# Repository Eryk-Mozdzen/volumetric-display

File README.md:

# Volumetric Display
Design inspired from [mitxela](https://www.youtube.com/watch?v=HKpBhE7QVAI).

### Specs
- STM32F030 microcontroller
- 8x8 led matrix
- CNY70 IR sensor
- 2x CR3032 power source

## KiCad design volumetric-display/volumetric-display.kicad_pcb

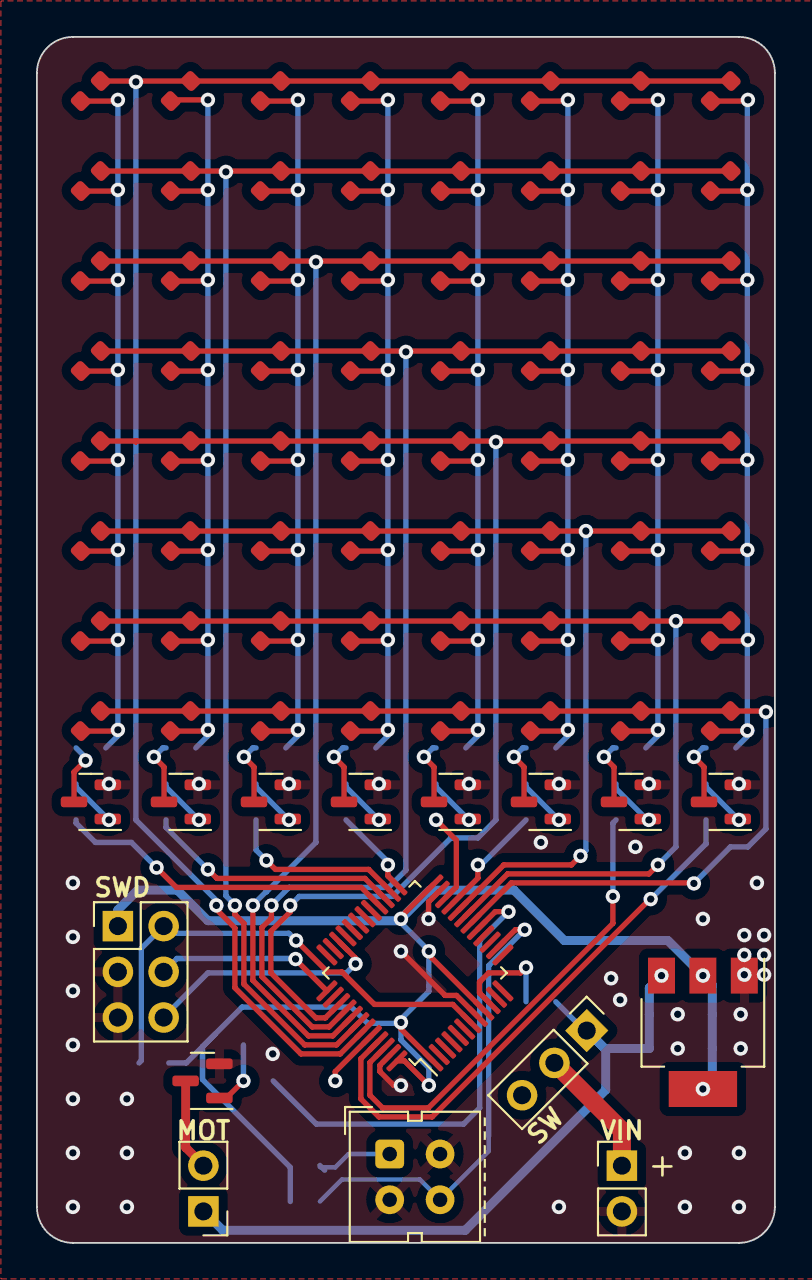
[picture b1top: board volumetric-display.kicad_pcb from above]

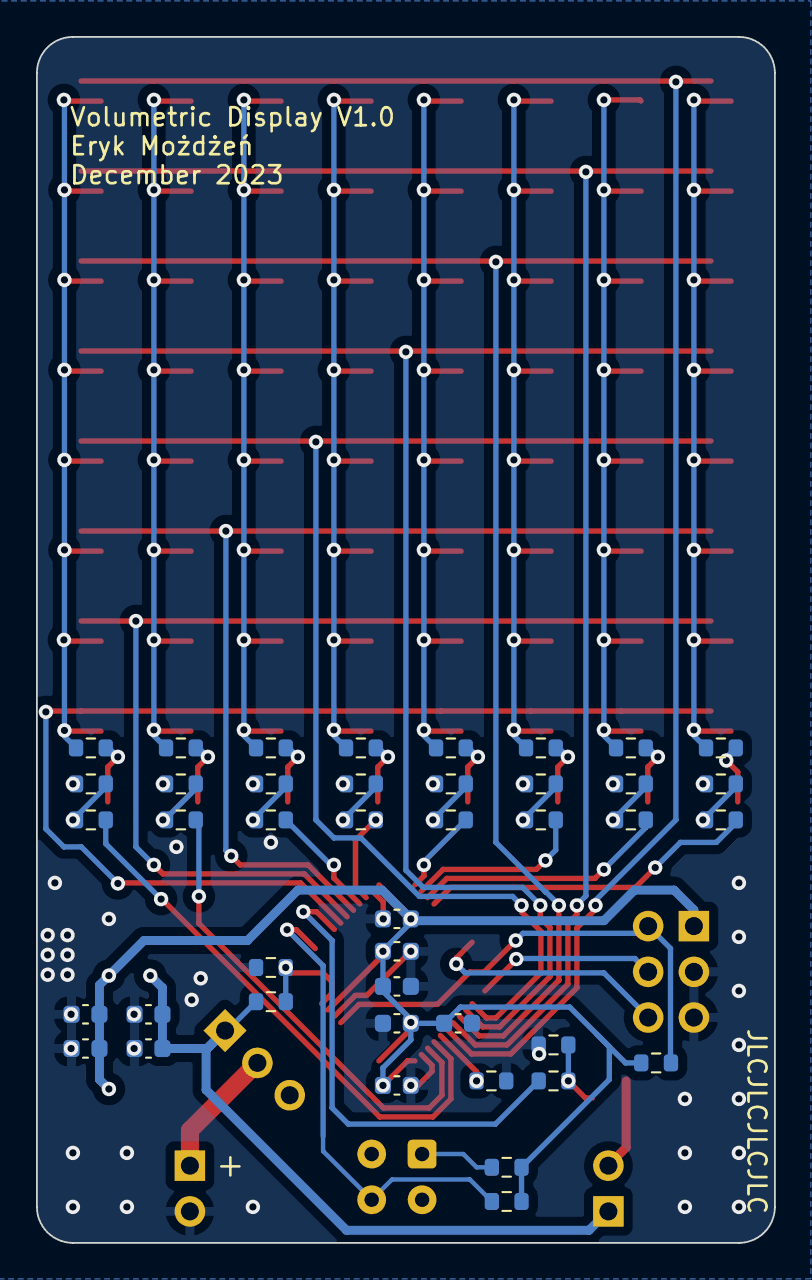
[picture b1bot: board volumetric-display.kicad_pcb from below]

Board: 2 copper layers, 41.0 x 67.0 mm, 122 parts (42 on the bottom side), 54 nets.

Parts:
C1, C7, C10: 4u7; C_0603_1608Metric
C2, C3, C4, C8, C9: 100n; C_0603_1608Metric
C5: 10n; C_0603_1608Metric
C6: 1u; C_0603_1608Metric
D1, D2, D3, D4, D5, D6, D7, D8, D9, D10, D11, D12, D13, D14, D15, D16, D17, D18, D19, D20, D21, D22, D23, D24, D25, D26, D27, D28, D29, D30, D31, D32, D33, D34, D35, D36, D37, D38, D39, D40, D41, D42, D43, D44, D45, D46, D47, D48, D49, D50, D51, D52, D53, D54, D55, D56, D57, D58, D59, D60, D61, D62, D63, D64: LED; led_0603
J1: Conn_02x03_Odd_Even; PinHeader_2x03_P2.54mm_Vertical
J2, J3: Conn_01x02; PinHeader_1x02_P2.54mm_Vertical
Q1, Q2, Q3, Q4, Q5, Q6, Q7, Q8, Q9: BSS138; SOT-23
R1, R7, R9, R10, R11, R12, R13, R14, R15, R16, R17, R18, R19, R20, R25, R26, R27, R28: 500; R_0603_1608Metric
R2, R3, R4, R8, R21, R22, R23, R24, R29, R30, R31, R32: 10k; R_0603_1608Metric
R5, R6: 100k; R_0603_1608Metric
SW1: SW_Push_SPDT; PinHeader_1x03_P2.54mm_Vertical
U1: CNY70; Vishay_CNY70
U2: STM32F030C8Tx; LQFP-48_7x7mm_P0.5mm
U3: LM1117MP-3.3; SOT-223-3_TabPin2

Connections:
+3.3V: C1.1, C2.1, C3.1, C4.1, C5.1, C6.1, C9.1, C10.1, J1.1, R1.1, R2.1, R3.2, U2.1 (VDD), U2.9 (VDDA), U2.24 (VDD), U2.48 (VDD), U3.2 (VO)
+BATT: C7.1, C8.1, J2.1, R5.1, SW1.1 (A), U3.3 (VI)
/BATT_SENSE: R5.2, R6.1, U2.10 (PA0)
/MATRIX_COL0: R17.1, U2.28 (PB15)
/MATRIX_COL1: R18.1, U2.27 (PB14)
/MATRIX_COL2: R19.1, U2.26 (PB13)
/MATRIX_COL3: R20.1, U2.25 (PB12)
/MATRIX_COL4: R25.1, U2.22 (PB11)
/MATRIX_COL5: R26.1, U2.21 (PB10)
/MATRIX_COL6: R27.1, U2.46 (PB9)
/MATRIX_COL7: R28.1, U2.45 (PB8)
/MATRIX_ROW0: D1.2 (A), D2.2 (A), D3.2 (A), D4.2 (A), D5.2 (A), D6.2 (A), D7.2 (A), D8.2 (A), U2.43 (PB7)
/MATRIX_ROW1: D9.2 (A), D10.2 (A), D11.2 (A), D12.2 (A), D13.2 (A), D14.2 (A), D15.2 (A), D16.2 (A), U2.42 (PB6)
/MATRIX_ROW2: D17.2 (A), D18.2 (A), D19.2 (A), D20.2 (A), D21.2 (A), D22.2 (A), D23.2 (A), D24.2 (A), U2.41 (PB5)
/MATRIX_ROW3: D25.2 (A), D26.2 (A), D27.2 (A), D28.2 (A), D29.2 (A), D30.2 (A), D31.2 (A), D32.2 (A), U2.40 (PB4)
/MATRIX_ROW4: D33.2 (A), D34.2 (A), D35.2 (A), D36.2 (A), D37.2 (A), D38.2 (A), D39.2 (A), D40.2 (A), U2.39 (PB3)
/MATRIX_ROW5: D41.2 (A), D42.2 (A), D43.2 (A), D44.2 (A), D45.2 (A), D46.2 (A), D47.2 (A), D48.2 (A), U2.20 (PB2)
/MATRIX_ROW6: D49.2 (A), D50.2 (A), D51.2 (A), D52.2 (A), D53.2 (A), D54.2 (A), D55.2 (A), D56.2 (A), U2.19 (PB1)
/MATRIX_ROW7: D57.2 (A), D58.2 (A), D59.2 (A), D60.2 (A), D61.2 (A), D62.2 (A), D63.2 (A), D64.2 (A), U2.18 (PB0)
/MOTOR: R7.1, U2.17 (PA7)
/RESET: J1.2, R3.1, U2.7 (NRST)
/SENSOR: R2.2, U1.3 (C), U2.14 (PA4)
/SWCLK: J1.4, U2.37 (PA14)
/SWDIO: J1.6, U2.34 (PA13)
/low_driver/OUT0: Q2.3 (D), R9.2
/low_driver/OUT1: Q3.3 (D), R10.2
/low_driver/OUT2: Q4.3 (D), R11.2
/low_driver/OUT3: Q5.3 (D), R12.2
/low_driver/OUT4: Q6.3 (D), R13.2
/low_driver/OUT5: Q7.3 (D), R14.2
/low_driver/OUT6: Q8.3 (D), R15.2
/low_driver/OUT7: Q9.3 (D), R16.2
GND: C1.2, C2.2, C3.2, C4.2, C5.2, C6.2, C7.2, C8.2, C9.2, C10.2, J1.3, J1.5, J3.2, Q1.2 (S), Q2.2 (S), Q3.2 (S), Q4.2 (S), Q5.2 (S), Q6.2 (S), Q7.2 (S), Q8.2 (S), Q9.2 (S), R4.1, R6.2, R8.2, R21.2, R22.2, R23.2, R24.2, R29.2, R30.2, R31.2, R32.2, U1.2 (K), U1.4 (E), U2.8 (VSSA), U2.23 (VSS), U2.47 (VSS), U3.1 (GND)
unnamed: D1.1 (K), D9.1 (K), D17.1 (K), D25.1 (K), D33.1 (K), D41.1 (K), D49.1 (K), D57.1 (K), R9.1
unnamed: D2.1 (K), D10.1 (K), D18.1 (K), D26.1 (K), D34.1 (K), D42.1 (K), D50.1 (K), D58.1 (K), R10.1
unnamed: D3.1 (K), D11.1 (K), D19.1 (K), D27.1 (K), D35.1 (K), D43.1 (K), D51.1 (K), D59.1 (K), R11.1
unnamed: D4.1 (K), D12.1 (K), D20.1 (K), D28.1 (K), D36.1 (K), D44.1 (K), D52.1 (K), D60.1 (K), R12.1
unnamed: D5.1 (K), D13.1 (K), D21.1 (K), D29.1 (K), D37.1 (K), D45.1 (K), D53.1 (K), D61.1 (K), R13.1
unnamed: D6.1 (K), D14.1 (K), D22.1 (K), D30.1 (K), D38.1 (K), D46.1 (K), D54.1 (K), D62.1 (K), R14.1
unnamed: D7.1 (K), D15.1 (K), D23.1 (K), D31.1 (K), D39.1 (K), D47.1 (K), D55.1 (K), D63.1 (K), R15.1
unnamed: D8.1 (K), D16.1 (K), D24.1 (K), D32.1 (K), D40.1 (K), D48.1 (K), D56.1 (K), D64.1 (K), R16.1
unnamed: J2.2, Q1.3 (D)
unnamed: J3.1, SW1.2 (B)
unnamed: Q1.1 (G), R7.2, R8.1
unnamed: Q2.1 (G), R17.2, R21.1
unnamed: Q3.1 (G), R18.2, R22.1
unnamed: Q4.1 (G), R19.2, R23.1
unnamed: Q5.1 (G), R20.2, R24.1
unnamed: Q6.1 (G), R25.2, R29.1
unnamed: Q7.1 (G), R26.2, R30.1
unnamed: Q8.1 (G), R27.2, R31.1
unnamed: Q9.1 (G), R28.2, R32.1
unnamed: R1.2, U1.1 (A)
unnamed: R4.2, U2.44 (BOOT0)

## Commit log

2023-12-17 add docs
